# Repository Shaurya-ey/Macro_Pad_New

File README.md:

# Macro_Pad_New
Working on a Macropad (Beginner Build).

## About The Project

### Project Description
- Dimensions:- 89.050 x 83.469 mm
- This is a Custom built 3×4 macropad built using the Seeed Studio XIAO RP2040
- Includes 12 mechanical keys and 1 rotary encoder
- It will help in multitasking, fast reflexes and especially for video editing, designing CAD models and Coding.
- This custom macropad can be switched between 3 modes, which are :-
  - Coding
  - Video Editing
  - Cad Modelling 
- The 3 LED'S are there for depicting in which mode we're in :-
  - RED   -> Video Editting
  - BLUE  -> CAD Modelling
  - GREEN -> Video Editting

### Why I Made This Project
- As i'm more into electronics, firmware development and soldering crazy stuffs.
- Wanted to learn something new like how to prepare schematics,routing for Pcb's.

### How to Use This Project
- Connect the macropad to your computer  theough a Type-C USB cable.
- The device is detected as a standard USB HID keyboard.
- The Keys and Rotary Encoder can be Reprogrammed for:
  - Shortcuts (i.e: Copy, paste shortcuts)
  - Music controls
  - Mode switching (Mine includes 3 modes)
- And for overall Firmware.

# 1. Overall Hackpad

# 2. Schematic

# 3. PCB Layout

# 4. Case and Assembly

# 5. Bill of Materials (BOM)
* 1x Seeed XIAO RP2040
* 1x EC11 Rotary Encoders
* 3x SK6812 MINI-E LEDs
* 12x 1N4148 Diodes 
* 12x MX-Style switches
* 4x M3x16mm screws

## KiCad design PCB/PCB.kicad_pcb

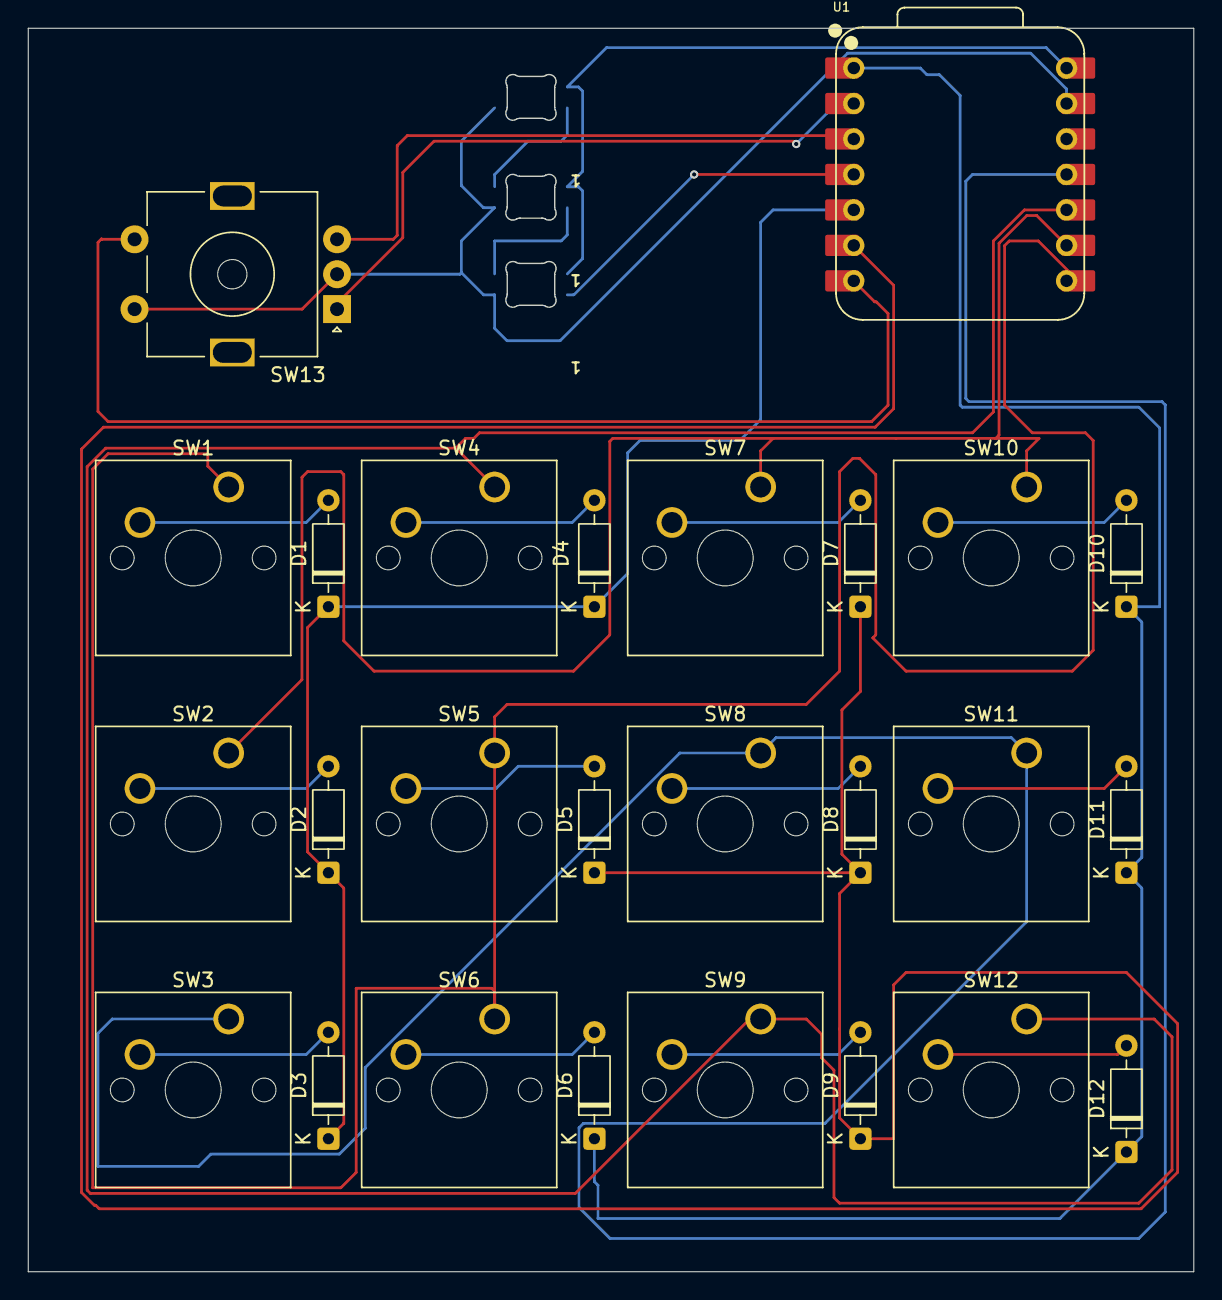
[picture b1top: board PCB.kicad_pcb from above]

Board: 2 copper layers, 83.5 x 89.0 mm, 29 parts (0 on the bottom side), 27 nets.

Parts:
D1, D2, D3, D4, D5, D6, D7, D8, D9, D10, D11, D12: 1N4148; D_DO-35_SOD27_P7.62mm_Horizontal
D13, D14, D15: SK6812MINI; MX_SK6812MINI-E_REV
SW1, SW2, SW3, SW4, SW5, SW6, SW7, SW8, SW9, SW10, SW11, SW12: SW_Push; SW_Cherry_MX_1.00u_PCB
SW13: RotaryEncoder_Switch; RotaryEncoder_Alps_EC11E-Switch_Vertical_H20mm_MountingHoles
U1: XIAO-RP2040-DIP

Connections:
+5V_LED: D13.4 (VDD), D14.4 (VDD), D15.4 (VDD), U1.14 (VBUS)
C1: SW1.1, SW5.1, SW6.1, U1.8 (GPIO1/RX)
C2: SW2.1, SW7.1, SW10.1, U1.9 (GPIO2/SCK)
C3: SW3.1, SW8.1, SW11.1, U1.11 (GPIO3/MOSI)
C4: SW4.1, SW9.1, SW12.1, U1.10 (GPIO4/MISO)
Dout: D15.3 (DIN), U1.4 (GPIO29/ADC3/A3)
E_A: SW13.A, U1.2 (GPIO27/ADC1/A1)
E_B: SW13.B, U1.3 (GPIO28/ADC2/A2)
E_S1: SW13.S1, U1.7 (GPIO0/TX)
GND: D13.2 (VSS), D14.2 (VSS), D15.2 (VSS), SW13.C, SW13.S2, U1.13 (GND)
unnamed: D1.2 (A), SW1.2
unnamed: D2.2 (A), SW2.2
unnamed: D3.2 (A), SW3.2
unnamed: D4.2 (A), SW4.2
unnamed: D5.2 (A), SW5.2
unnamed: D6.2 (A), SW6.2
unnamed: D7.2 (A), SW7.2
unnamed: D8.2 (A), SW8.2
unnamed: D9.2 (A), SW9.2
unnamed: D10.2 (A), SW10.2
unnamed: D11.2 (A), SW11.2
unnamed: D12.2 (A), SW12.2
unnamed: D13.3 (DIN), D15.1 (DOUT)
unnamed: D13.1 (DOUT), D14.3 (DIN)
R1: D1.1 (K), D2.1 (K), D3.1 (K), D4.1 (K), U1.5 (GPIO6/SDA)
R2: D5.1 (K), D7.1 (K), D8.1 (K), D9.1 (K), U1.6 (GPIO7/SCL)
R3: D6.1 (K), D10.1 (K), D11.1 (K), D12.1 (K), U1.1 (GPIO26/ADC0/A0)

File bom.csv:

Designator,Footprint,Quantity,Value,LCSC Part #
"D1, D10, D11, D12, D2, D3, D4, D5, D6, D7, D8, D9",D_DO-35_SOD27_P7.62mm_Horizontal,12,1N4148,
"D13, D14, D15",MX_SK6812MINI-E_REV,3,SK6812MINI,
"SW1, SW10, SW11, SW12, SW2, SW3, SW4, SW5, SW6, SW7, SW8, SW9",SW_Cherry_MX_1.00u_PCB,12,SW_Push,
SW13,RotaryEncoder_Alps_EC11E-Switch_Vertical_H20mm_MountingHoles,1,RotaryEncoder_Switch,
U1,XIAO-RP2040-DIP,1,XIAO-RP2040-DIP,

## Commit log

2026-02-04 Create CAD
2026-02-04 Create temp
